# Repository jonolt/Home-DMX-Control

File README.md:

# Home DMC Controll - DONT USE!
**Dont use the data in this repository. Board and Software are not well designed.**

Improved Project was moved to 2 seperate repositories:
- [Home-DMX-Board](https://github.com/jonolt/Home-DMX-Board)
- [Home-DMX-Firmaware](https://github.com/jonolt/Home-DMX-Firmaware)

is a simple arduino based DMX controller to controll led lights installed in your home to be used with DMX controllers and relais.

## Idea

The selection for the lighting scene in daily use should be as simple as possible. Therefore exactly two push buttons are used to move up and down in a list of lighting scenes. Since I am not a fan of idle transformers, a conventional light switch is used in my application to switch the whole system on and off. In the same way a corresponding scene could be set.

The individual scenes should be adjustable directly on the controller without additional hardware. The input of the scenes works like on lighting control desks without motor faders via potentiometer and buttons. To make the firmware easy (without programmer and co) and maintainable by everyone, an Arduino was used, because it has a USB converter and the IDE is easy to use and install.

## End User Usage

### Everyay Usage

Use the two buttons (connecte do SW2 and SW3 on pcb) to change sceene, by going up and down an scene list.

### Configuration

Exact User Interface depends on the project specific arduino programm. The brigness values are set with two analog potis (one for each line). They work like in Ligthning Cosoles. A arrow up/down means the current poti value is below/above the software value. Chhanfing the poti value will not change the software value until bot values where matched once. This is shown when only a pipe is displayed.

#### Page 0

It is used to adjust the brightness of the display and to show the temperature measured by the I2C temperature sensor.

#### Page X (1, ..., 9)

Each page stores one light scene. In my project I have 3 zones of WW/CW LED stripes which should be switched independently. The zones are divided into columns. With SW1 a column can be selected and with RV1 and RV2 the brightness can be adjusted. To switch pages SW2 and SW3 are used which are not on the board. 

## Hard- and Software

### Hardware

Because I want to see if my hardware is running I have a power LED (D4) and a status LED (D5), which is switched on and off in my loop. This may cost an I/O pin, but you can always see if the firmware is running properly.

The MAX481 (U2) is a transceiver for RS-485 and RS-422 communication based on DMX. It uses the TX and RX pins of the arduino. For a visual control of the DMX communication 2x2 (overkill) leds are connected via buffer (U4).

The display is controlled serially via the library provided by the manufacturer.

Since only one interrupt is available when using IC2, all three switches are connected to it via diodes (D1, D2, D3) and the pressed switch is determined in the ISR. The switches are already hardware debaunced.

The I2C temperature sensor can be used for an emergency shutdown, or as I use it, just to see how warm it is in the chamber with the transformers (I trust the thermal protection of the power supplies).

### Software

The scenes and the current page and current column are stored in the EPPROM. Each page/scene has in the current implementation 10 8-bit registers to store DMX values. These can be accessed by adding the number of the register to the start address of the page, where the start address depends on the current page.

The Main Loop consists of 4 parts

1. Check whether a switch has been pressed and do according action
2. Check whether the potentiometer value has changed and whether the value must be adopted and update the display
3. Write DMX values
4. Toogle status LED

Code is more or less self explaining (sorry for the a bit cryptic math logic for pages). Be aware of the pointers in the trace method.

## Project Example

## Licence

See subfolders for indiviadual licences for each part of this project.

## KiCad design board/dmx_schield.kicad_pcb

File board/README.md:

## License and Copyright

Copyright (C) 2019, 2020 Johannes N.
 
This program is free software: you can redistribute it and/or modify
it under the terms of the GNU General Public License as published by
the Free Software Foundation, version 2.1 only.

This program is distributed in the hope that it will be useful,
but WITHOUT ANY WARRANTY; without even the implied warranty of
MERCHANTABILITY or FITNESS FOR A PARTICULAR PURPOSE.  See the
GNU General Public License for more details.

You should have received a copy of the GNU General Public License
along with this program.  If not, see <https://www.gnu.org/licenses/>.

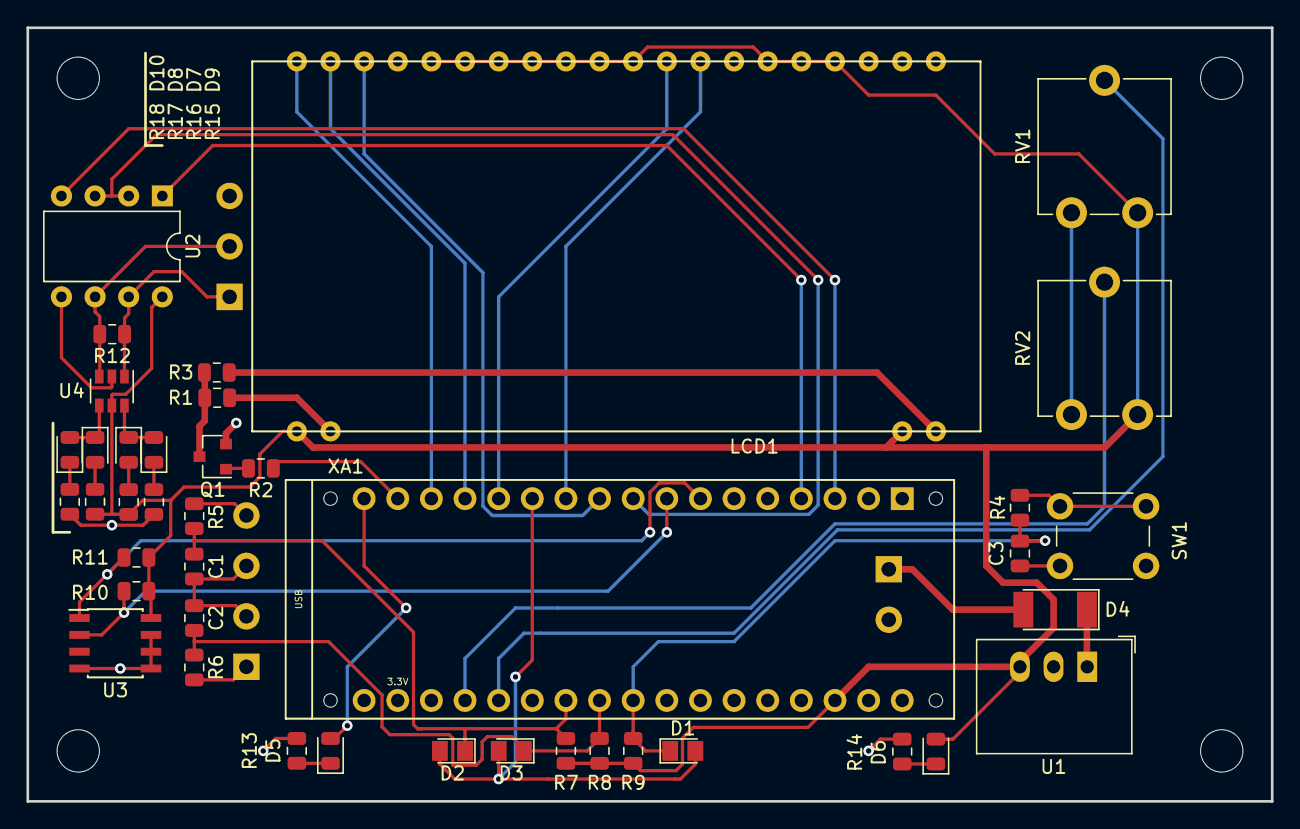
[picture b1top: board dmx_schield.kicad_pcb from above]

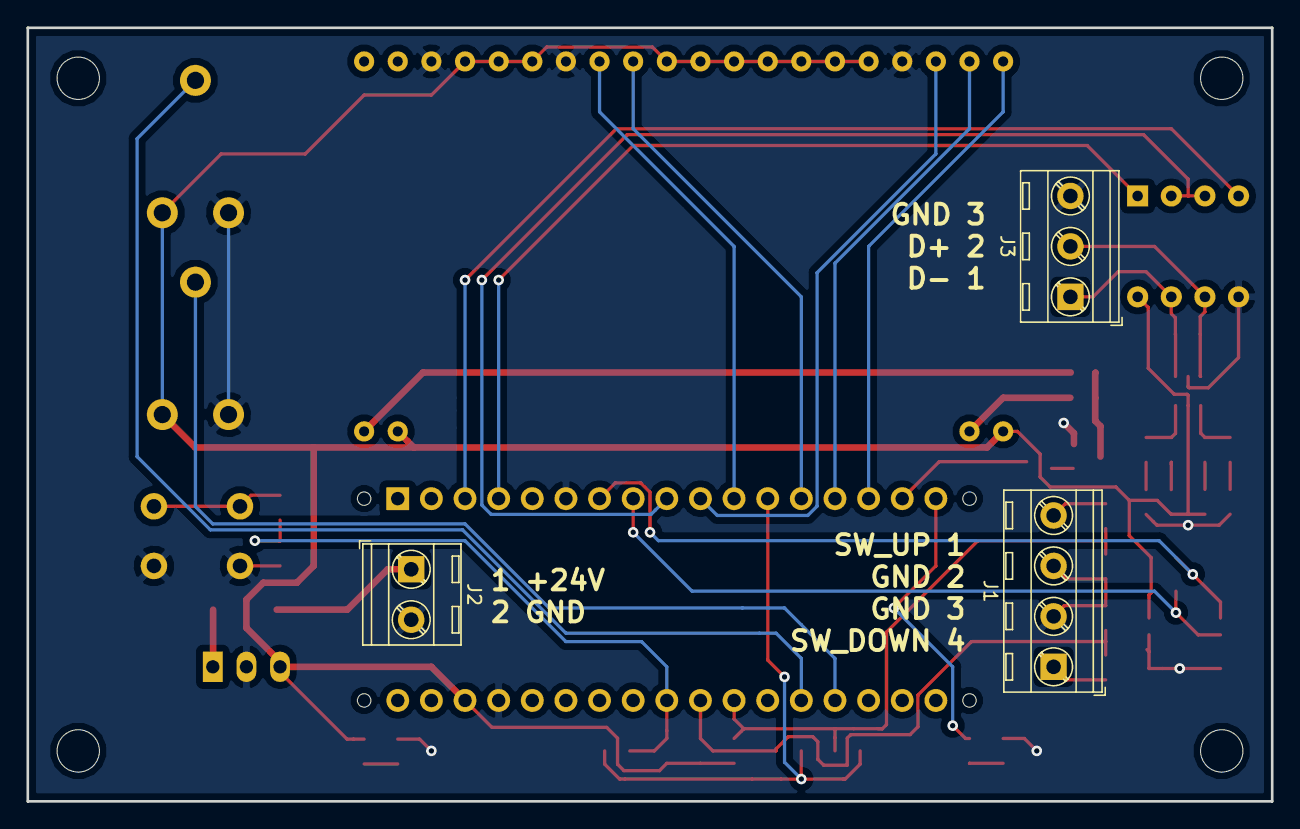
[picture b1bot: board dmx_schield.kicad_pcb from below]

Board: 2 copper layers, 94.0 x 58.4 mm, 48 parts (3 on the bottom side), 39 nets.

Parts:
C1, C2, C3: 1u; C_0805_2012Metric
D1, D2, D3: BAS85; D_MicroMELF
D4: 1N4001; D_MELF
D5, D6, D7, D8, D9, D10: LED; LED_0805_2012Metric
H1, H2, H3, H4: MountingHole; MountingHole_3.2mm_M3_DIN965
J1: Screw_Terminal_01x04; TerminalBlock_MetzConnect_Type086_RT03404HBLC_1x04_P3.81mm_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
J2: Screw_Terminal_01x02; TerminalBlock_MetzConnect_Type086_RT03402HBLC_1x02_P3.81mm_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
J3: Screw_Terminal_01x03; TerminalBlock_MetzConnect_Type086_RT03403HBLC_1x03_P3.81mm_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
LCD1: EADOGM162; EA DOGM 162
Q1: BSR14; SOT-23
R1, R3: 56; R_0805_2012Metric
R2, R4, R5, R6: 1,0k; R_0805_2012Metric
R7, R8, R9: 10k; R_0805_2012Metric
R10, R11: 4,7k; R_0805_2012Metric
R12: 120; R_0805_2012Metric
R13, R14, R15, R16, R17, R18: 100; R_0805_2012Metric
RV1, RV2: 10k; Potentiometer_ACP_CA9-V10_Vertical
SW1: SW_Push; SW_PUSH_6mm_H5mm
U1: R-78E5.0-0.5; Converter_DCDC_RECOM_R-78E-0.5_THT
U2: MAX481E; DIP-8_W7.62mm
U3: LM75B; SOIC-8_3.9x4.9mm_P1.27mm
U4: 74LVC2G34; SOT-23-6
XA1: Arduino_Micro_Socket

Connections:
/CLK: LCD1.29, XA1.D8
/CS: LCD1.38, XA1.D5
/INTERUPT: D1.2, D2.2, D3.2, XA1.D7
/LED: R2.1, XA1.D11
/POTI_KW: RV2.2, XA1.A0
/POTI_WW: RV1.2, XA1.A1
/REDE: U2.2, U2.3, XA1.D4
/RESET: LCD1.40, XA1.D10
/RS: LCD1.39, XA1.D9
/SI: LCD1.28, XA1.D6
/SW_COL: C3.1, D1.1, R4.1, R9.1, XA1.A5
/SW_KW: C2.2, D3.1, R6.1, R8.1, XA1.A4
/SW_WW: C1.1, D2.1, R5.1, R7.1, XA1.A3
GND: C1.2, C2.1, C3.2, J1.2, J1.3, J2.2, J3.3, LCD1.23, LCD1.27, LCD1.37, Q1.2, R13.2, R14.2, R15.1, R18.1, RV1.3, RV2.3, SW1.1, U1.2, U2.5, U3.4, U3.5, U3.6, U3.7, U4.2, XA1.GND1, XA1.GND2
unnamed: D4.1, U1.1
unnamed: D4.2, J2.1
unnamed: D5.1, R13.1
unnamed: D5.2, XA1.D12
unnamed: D6.1, R14.1
unnamed: D7.1, D9.2, U4.6
unnamed: D7.2, R16.2
unnamed: D8.2, R17.2
unnamed: D9.1, R15.2
unnamed: D10.1, R18.2
unnamed: D8.1, D10.2, U4.4
unnamed: J1.1, R6.2
unnamed: J1.4, R5.2
unnamed: J3.1, R12.1, U2.7, U4.1
unnamed: J3.2, R12.2, U2.6, U4.3
unnamed: LCD1.2, R1.1
unnamed: LCD1.20, R3.1
unnamed: Q1.1, R2.2
unnamed: Q1.3, R1.2, R3.2
unnamed: R4.2, SW1.2
unnamed: R10.2, U3.2, XA1.D3
unnamed: R11.2, U3.1, XA1.D2
unnamed: U2.1, XA1.D0
unnamed: U2.4, XA1.D1
VCC: D6.2, LCD1.1, LCD1.19, LCD1.24, LCD1.25, LCD1.26, LCD1.30, LCD1.31, LCD1.32, LCD1.33, LCD1.34, LCD1.35, LCD1.36, R7.2, R8.2, R9.2, R10.1, R11.1, R16.1, R17.1, RV1.1, RV2.1, U1.3, U2.8, U3.8, U4.5, XA1.VIN

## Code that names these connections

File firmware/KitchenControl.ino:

/*
 * Copyright (C) 2019, 2020 Johannes N.
 * 
 * This program is free software: you can redistribute it and/or modify
 * it under the terms of the GNU General Public License as published by
 * the Free Software Foundation, version 2.1 only.
 *
 * This program is distributed in the hope that it will be useful,
 * but WITHOUT ANY WARRANTY; without even the implied warranty of
 * MERCHANTABILITY or FITNESS FOR A PARTICULAR PURPOSE.  See the
 * GNU General Public License for more details.
 *
 * You should have received a copy of the GNU General Public License
 * along with this program.  If not, see <https://www.gnu.org/licenses/>.
 */

#include <Arduino.h>
#include <SPI.h>
#include <EEPROM.h>
#include <DMXSerial.h>
#include <Temperature_LM75_Derived.h>
#include "dogm_7036.h"

#define LM75_ADDRESS 0x48

#define PIN_BACKLIGHT 11
#define PIN_LED_STATUS 12
#define PIN_ARDUINO_LED 13
#define PIN_POTI_KW A0
#define PIN_POTI_WW A1
#define PIN_INTERUPT 7
#define PIN_SW_UP A3
#define PIN_SW_DOWN A4
#define PIN_SW_COL A5

#define PIN_R232_REDE 4

#define EPPROM_BACKLIGHT 1
#define EEPROM_PAGE 0
#define EPROME_COL 2


//Display
dogm_7036 DOG;
byte DOG_ARROW_POS[] = {5, 9, 13};
byte arrow_none[] = {0x01, 0x01, 0x01, 0x01, 0x01, 0x01, 0x01, 0x01};
byte arrow_up[] = {0x01, 0x03, 0x05, 0x01, 0x01, 0x01, 0x01, 0x01};
byte arrow_down[] = {0x01, 0x01, 0x01, 0x01, 0x01, 0x05, 0x03, 0x01};

//Aquire Value
bool trace_ww = false;
bool trace_kw = false;
bool trace_start = false;
volatile bool isr_triggered = false;
volatile bool isr_state_sw_up = true;
volatile bool isr_state_sw_down = true;
volatile bool isr_state_sw_col= true;


//Others
bool status_led = true;
Generic_LM75 temperature(LM75_ADDRESS);


//Function
void writeDMX();
void set_toogle_status_led();
void trace(byte addr, byte poti_val, bool trace);
void isr();
byte get_addr_start();
byte get_poti_ww_value();
byte get_poti_kw_value();
byte get_poti_value(int pin);
void set_backlight();


void setup() {

  //Setup Display
  DOG.initialize(5, 6, 8, 9, 10, 1, DOGM162); //byte p_cs, byte p_si, byte p_clk, byte p_rs, byte p_res, boolean sup_5V, byte lines
  DOG.displ_onoff(true);
  DOG.cursor_onoff(false);
  DOG.define_char(0, arrow_none);
  DOG.define_char(1, arrow_up);
  DOG.define_char(2, arrow_down);

  //Setup Pins
  pinMode(PIN_BACKLIGHT, OUTPUT);
  digitalWrite(PIN_BACKLIGHT, HIGH);
  pinMode(PIN_LED_STATUS, OUTPUT);
  digitalWrite(PIN_LED_STATUS, HIGH);
  pinMode(PIN_R232_REDE, OUTPUT);
  digitalWrite(PIN_R232_REDE, HIGH);
  pinMode(PIN_SW_COL, INPUT);
  pinMode(PIN_SW_UP, INPUT);
  pinMode(PIN_SW_DOWN, INPUT);
  pinMode(PIN_INTERUPT, INPUT);
  pinMode(PIN_INTERUPT, INPUT_PULLUP);
  attachInterrupt(digitalPinToInterrupt(PIN_INTERUPT), isr, FALLING);

  //Setup EPPROM
  if (EEPROM.read(EEPROM_PAGE) > 9) {
    EEPROM.write(EEPROM_PAGE, 0);
  }
  if (EEPROM.read(EPROME_COL) > 2) {
    EEPROM.write(EPROME_COL, 0);
  }
  EEPROM.write(100, 0);
  EEPROM.write(101, 0);
  EEPROM.write(102, 0);
  EEPROM.write(103, 0);
  EEPROM.write(104, 0);
  EEPROM.write(105, 0);

  //Setup Communiication (DMX, Serial)
  DMXSerial.init(DMXController);
  Wire.begin();

}


void loop() {
  if(isr_triggered){
    delay(50);
    handle_isr();
  } 
  set_backlight();
  if (EEPROM.read(EEPROM_PAGE) != 0) {
    digitalWrite(PIN_ARDUINO_LED, LOW);
    int addr = get_addr_start();
    String strW = "S WW";
    String strK = String(EEPROM.read(EEPROM_PAGE));
    strK.concat(" KW");
    for (int i = 0; i < 3; i++) {
      char buf[3];
      sprintf(buf, " %03d", EEPROM.read(addr + 2 * i));
      strW.concat(buf);
      sprintf(buf, " %03d", EEPROM.read(addr + 2 * i + 1));
      strK.concat(buf);
    }
    DOG.position(1, 1);
    DOG.string(strW.c_str());
    DOG.position(1, 2);
    DOG.string(strK.c_str());
    byte col = EEPROM.read(EPROME_COL);
    DOG.position(DOG_ARROW_POS[col], 1);
    trace(addr + 2 * col, get_poti_ww_value(), &trace_ww);
    DOG.position(DOG_ARROW_POS[col], 2);
    trace(addr + 2 * col + 1, get_poti_kw_value(), &trace_kw);
    delay(100);
  }
  else
  {
    digitalWrite(PIN_ARDUINO_LED, HIGH);
    DOG.position(1, 1);
    DOG.string("S Temp:        C");
    DOG.position(11, 1);
    DOG.string(String(temperature.readTemperatureC(), 1).c_str());
    DOG.position(1, 2);
    DOG.string("0 intesity:");
    char buf[3];
    sprintf(buf, " %03d   ", EEPROM.read(EPPROM_BACKLIGHT));
    DOG.string(buf);
    DOG.position(12, 2);
    trace(EPPROM_BACKLIGHT, get_poti_kw_value(), &trace_start);
    delay(50);
  }
  writeDMX();
  set_toogle_status_led();
}

void writeDMX() {
  //send values from EPPROM to dimmer
  int addr = get_addr_start();
  //RegalUnten
  DMXSerial.write(1, EEPROM.read(addr + 0));
  DMXSerial.write(2, EEPROM.read(addr + 1));
  //RegalOben
  DMXSerial.write(3, EEPROM.read(addr + 2));
  DMXSerial.write(4, EEPROM.read(addr + 3));
  //Glasswand
  DMXSerial.write(5, EEPROM.read(addr + 4));
  DMXSerial.write(6, EEPROM.read(addr + 4));
  DMXSerial.write(7, EEPROM.read(addr + 5));
  DMXSerial.write(8, EEPROM.read(addr + 5));
}

void set_toogle_status_led() {
  //Toogle Statu LED (blinking)
  if (status_led) {
    status_led = false;
  } else {
    status_led = true;
  }
  digitalWrite(PIN_LED_STATUS, status_led);
}


void trace(byte addr, byte poti_val, bool* trace) {
  //compare register value and poti value, writes poti value into
  //EEPROMafter being eqaul for the first time
  if (*trace) {
    EEPROM.write(addr, poti_val);
    DOG.ascii(0);
  }
  else
  {
    byte val_ist = EEPROM.read(addr);
    if (poti_val >= val_ist - 2 && poti_val <= val_ist + 2) {
      *trace = true;
    } else if (poti_val < val_ist) {
      DOG.ascii(1);
    } else {
      DOG.ascii(2);
    }
  }
}

void isr(){
  isr_triggered = true;
  isr_state_sw_up   = digitalRead(PIN_SW_UP);
  isr_state_sw_down = digitalRead(PIN_SW_DOWN);
  isr_state_sw_col  = digitalRead(PIN_SW_COL);
}

void handle_isr() {
  //process all key pressses. Changes page or column.
  //detachInterrupt(digitalPinToInterrupt(PIN_INTERUPT));
  delayMicroseconds(20000);
  if (!isr_state_sw_col) {
    byte col = EEPROM.read(EPROME_COL);
    col++;
    if (col > 2) {
      col = 0;
    }
    EEPROM.write(EPROME_COL, col);
  } else {
    int page = EEPROM.read(EEPROM_PAGE);
    if (!isr_state_sw_up) {
      page++;
    } else if (!isr_state_sw_down) {
      page--;
    }
    if (page > 9) {
      page = 0;
    }
    if (page < 0) {
      page = 9;
    }
    EEPROM.write(EEPROM_PAGE, page);
  }
  trace_ww = false;
  trace_kw = false;
  trace_start = false;
  isr_triggered = false;
  //delay(100);
  //attachInterrupt(digitalPinToInterrupt(PIN_INTERUPT), isr, FALLING);
}

byte get_addr_start() {
  //returns start epprom address for values of current page
  return EEPROM.read(EEPROM_PAGE) * 10 + 100;
}

byte get_poti_ww_value() {
  //returns a 8bit value for the ww (RV1) poti
  return get_poti_value(PIN_POTI_WW);
}

byte get_poti_kw_value() {
  //returns a 8bit value for the kw (RV2) poti
  return get_poti_value(PIN_POTI_KW);
}

inline byte get_poti_value(int pin) {
  //returns a 8bit value for the poti
  return analogRead(pin) / 4;
}

void set_backlight() {
  analogWrite(PIN_BACKLIGHT, EEPROM.read(EPPROM_BACKLIGHT));
}

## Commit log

2020-04-18 updated board (V1.1), improved readme
2020-05-01 extended and isolated V1.0
    added isolation to all elements connected to the outside world.
    PCB is now a multi purpose board with as many pins as possible
    available via the PCB.
    I'm not happy with the PWM output stage and the connector size.
    This may be changed.
2020-05-03 fixed footprint SIL7, minor improvements, updated doc
    fixed wrong pinout of SIL7 footprints and improved genral bnoard
    layout and silk layer. Completed description of hardware. Added
    a ods with the article numbers of the parts ordered @ reichelt.de.
    This PCB verision will be manufactured and unploaded to aisler.net.
